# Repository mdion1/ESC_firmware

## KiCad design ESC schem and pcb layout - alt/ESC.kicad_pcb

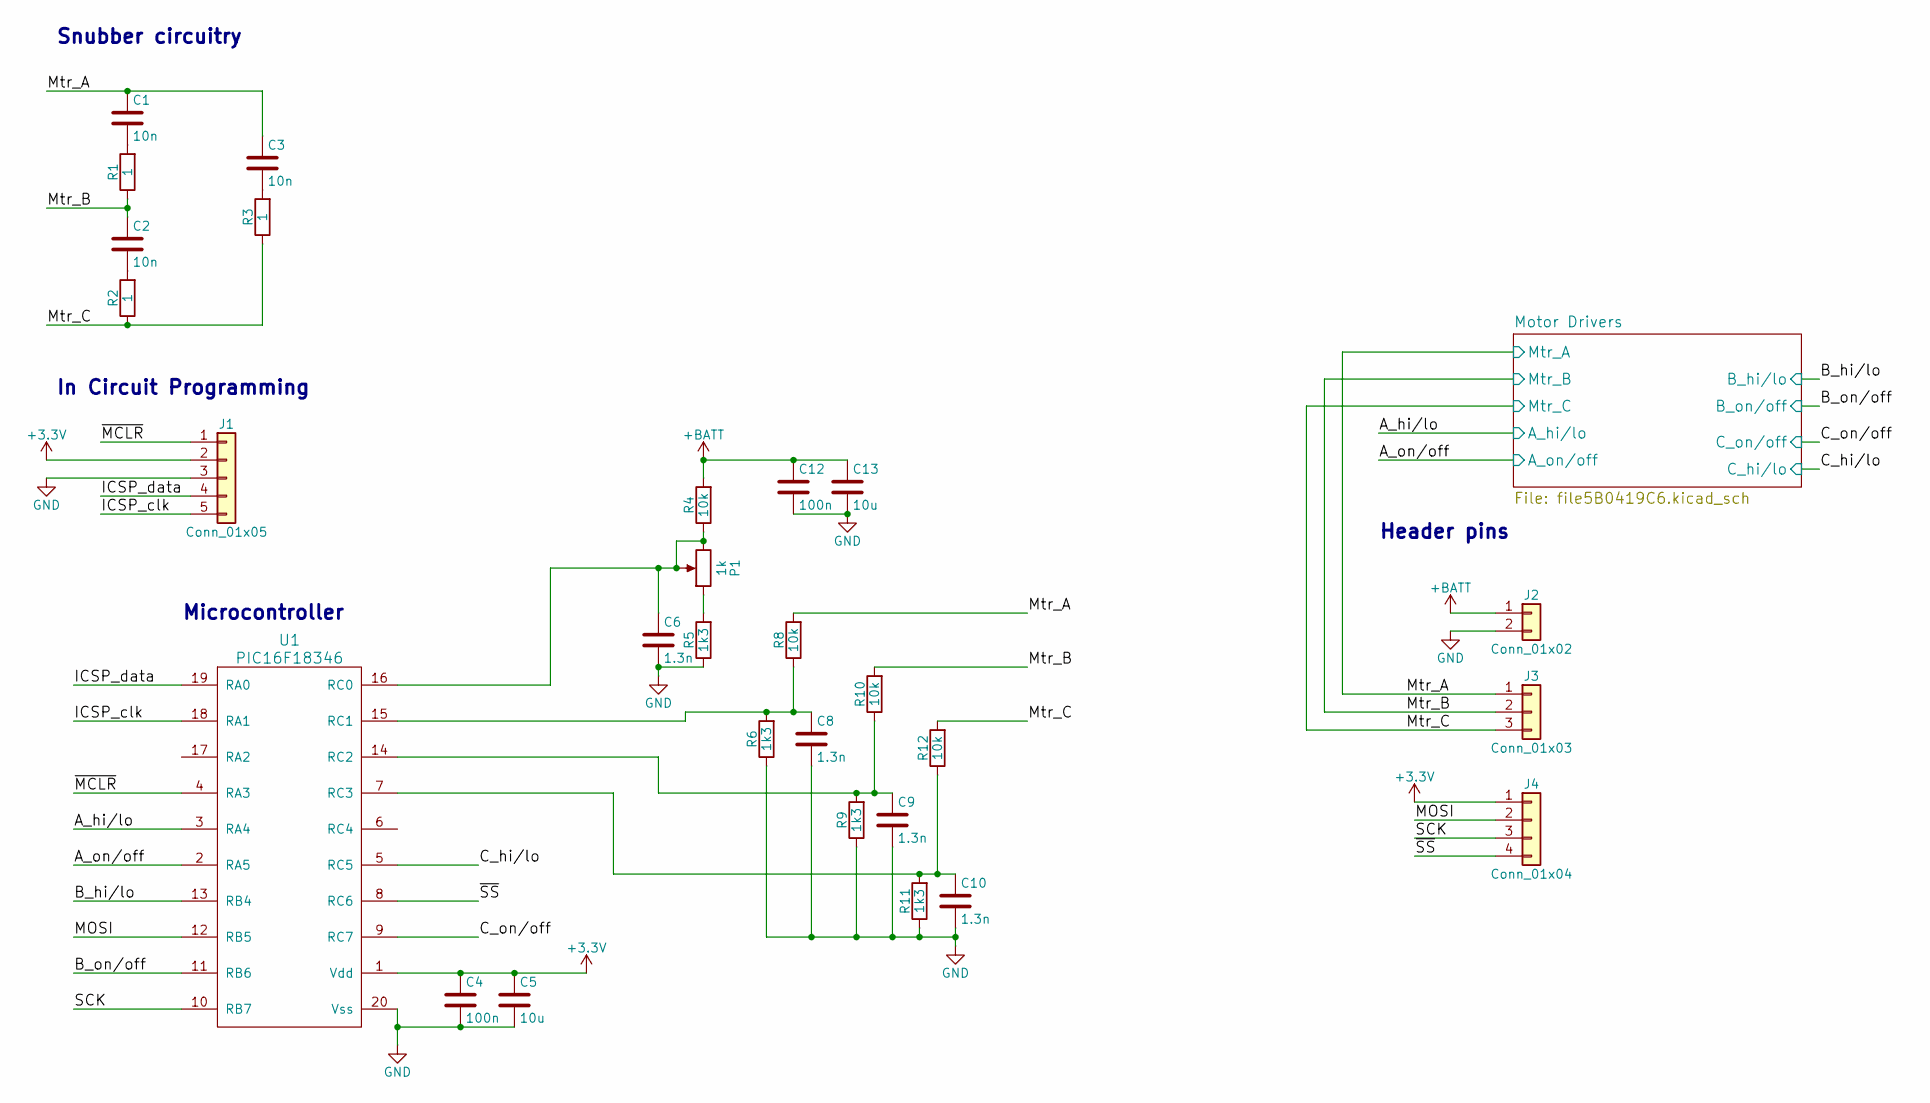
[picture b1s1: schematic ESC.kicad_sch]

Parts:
C1, C2, C3: 10n; C_0603_HandSoldering
C4, C12: 100n; C_0603_HandSoldering
C5, C13: 10u; C_0603_HandSoldering
C6, C8, C9, C10: 1.3n; C_0603_HandSoldering
J1: Conn_01x05; Male_header_pins_1x5
J2: Conn_01x02; Wire-to-board_1x2
J3: Conn_01x03; Wire-to-board_1x3
J4: Conn_01x04; Wire_to_board_cluster__4
P1: 1k; Potentiometer_Trimmer_Bourns_3223W
R1, R2, R3: 1; R_0603_HandSoldering
R4, R8, R10, R12: 10k; R_0603_HandSoldering
R5, R6, R9, R11: 1k3; R_0603_HandSoldering
U1: PIC16F18346; SOIC-20W_7.5x12.8mm_Pitch1.27mm

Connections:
+3V3: C4.1, C5.1, J1.2, J4.1, U1.1 (Vdd)
+BATT: C12.1, C13.1, J2.1, R4.2; also elsewhere on the board
/A_hi/lo: U1.3 (RA4); also elsewhere on the board
/A_on/off: U1.2 (RA5); also elsewhere on the board
/B_hi/lo: U1.13 (RB4); also elsewhere on the board
/B_on/off: U1.11 (RB6); also elsewhere on the board
/C_hi/lo: U1.5 (RC5); also elsewhere on the board
/C_on/off: U1.9 (RC7); also elsewhere on the board
/ICSP_clk: J1.5, U1.18 (RA1)
/ICSP_data: J1.4, U1.19 (RA0)
/MOSI: J4.2, U1.12 (RB5)
/Mtr_A: C1.1, C3.1, J3.1, R8.2; also elsewhere on the board
/Mtr_B: C2.1, J3.2, R1.1, R10.2; also elsewhere on the board
/Mtr_C: J3.3, R2.1, R3.1, R12.2; also elsewhere on the board
/SCK: J4.3, U1.10 (RB7)
/~MCLR: J1.1, U1.4 (RA3)
/~SS: J4.4, U1.8 (RC6)
GND: C4.2, C5.2, C6.2, C8.2, C9.2, C10.2, C12.2, C13.2, J1.3, J2.2, R5.1, R6.1, R9.1, R11.1, U1.20 (Vss); also elsewhere on the board
unnamed: C1.2, R1.2
unnamed: C2.2, R2.2
unnamed: C3.2, R3.2
unnamed: C6.1, P1.2, P1.3, R4.1, U1.16 (RC0)
unnamed: C8.1, R6.2, R8.1, U1.15 (RC1)
unnamed: C9.1, R9.2, R10.1, U1.14 (RC2)
unnamed: C10.1, R11.2, R12.1, U1.7 (RC3)
unnamed: P1.1, R5.2

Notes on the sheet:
In Circuit Programming
Header pins
Microcontroller
Snubber circuitry

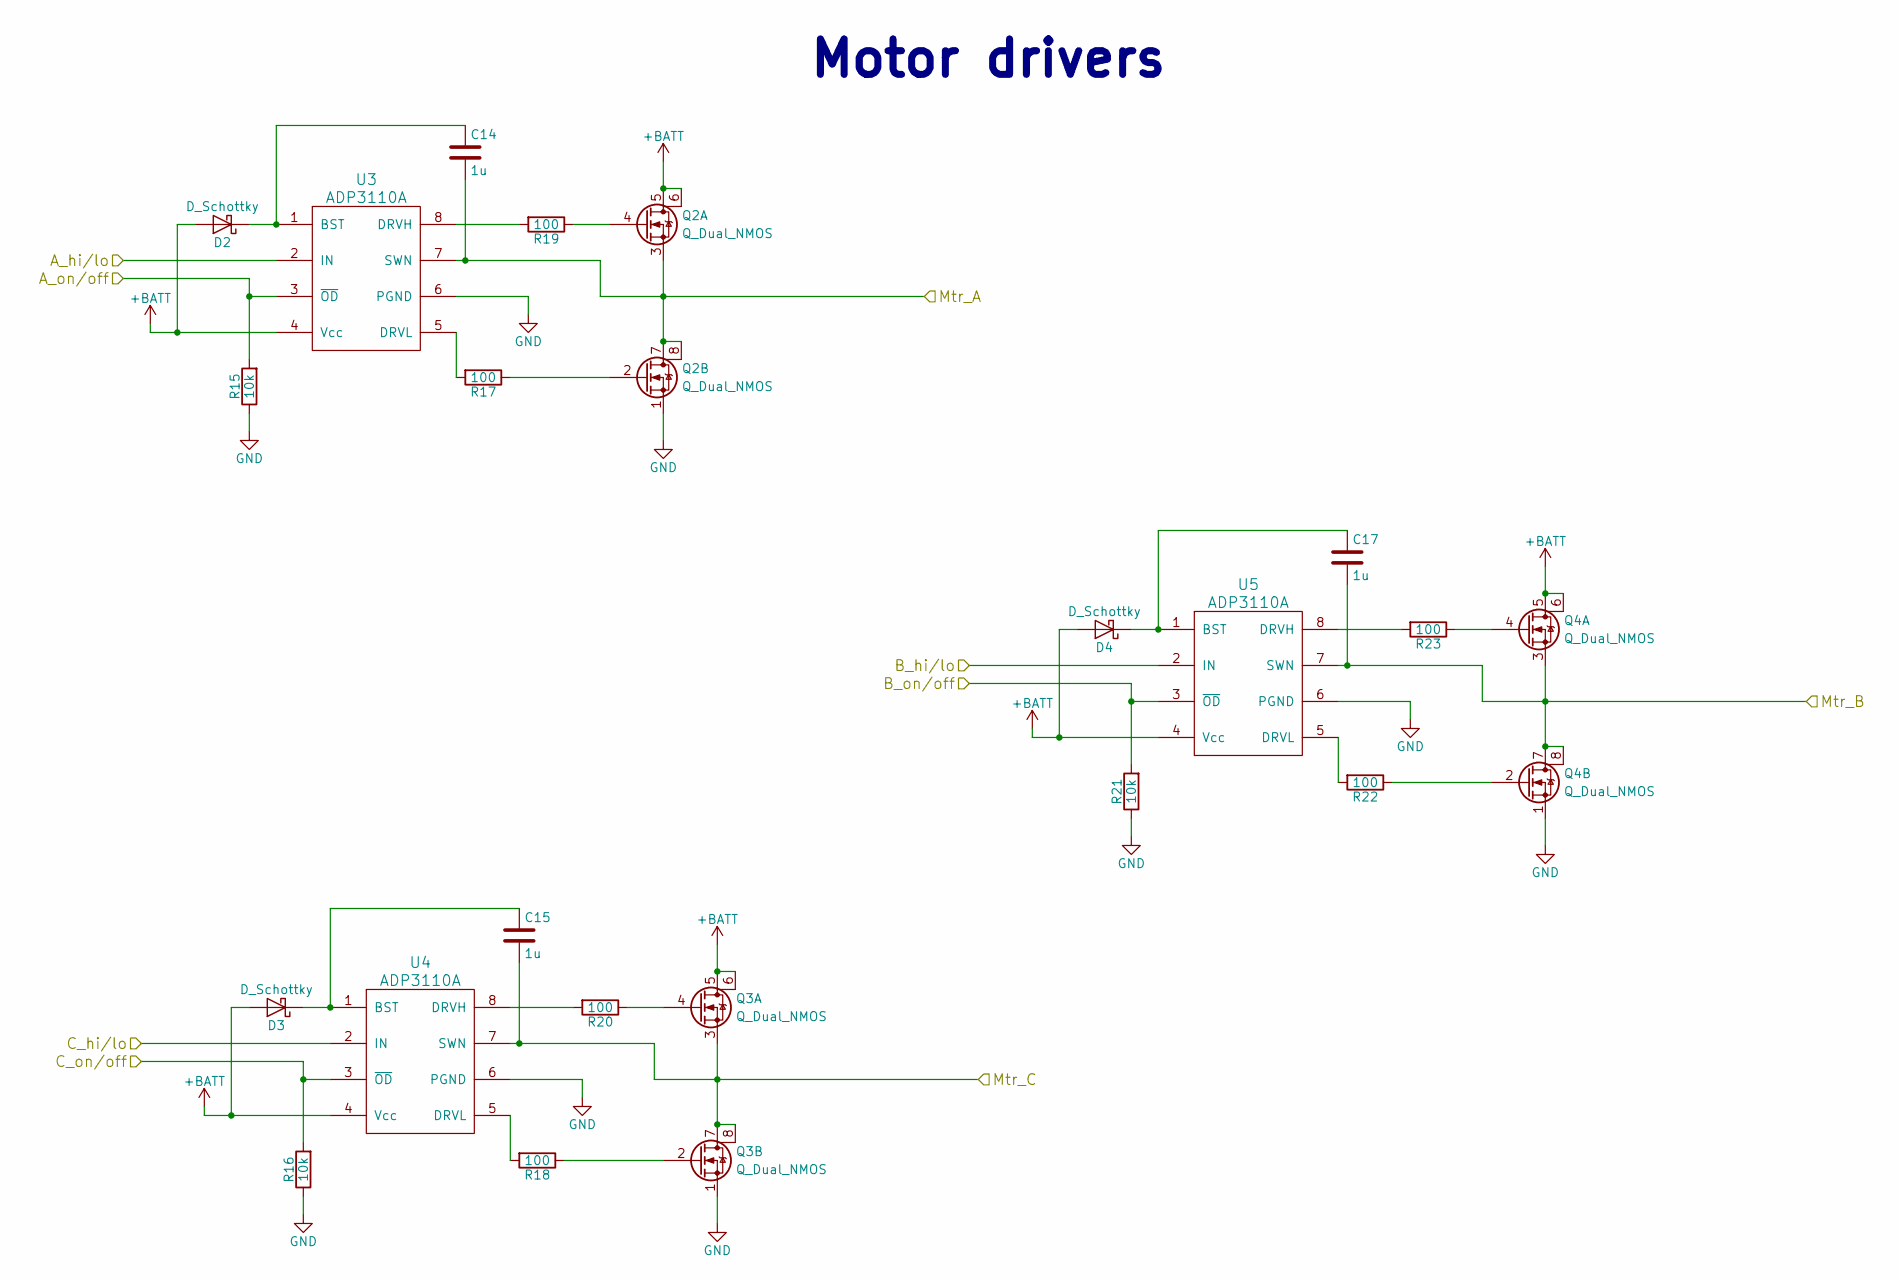
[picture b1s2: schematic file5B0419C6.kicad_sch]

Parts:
C14, C15, C17: 1u; C_0603_HandSoldering
D2, D3, D4: D_Schottky; D_0603
Q2, Q3, Q4: Q_Dual_NMOS; SOIC-8_3.9x4.9mm_Pitch1.27mm
R15, R16, R21: 10k; R_0603_HandSoldering
R17, R18, R19, R20, R22, R23: 100; R_0603_HandSoldering
U3, U4, U5: ADP3110A; SOIC-8_3.9x4.9mm_Pitch1.27mm

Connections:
+BATT: D2.2 (A), D3.2 (A), D4.2 (A), Q2.5 (D1), Q2.6 (D2), Q3.5 (D1), Q3.6 (D2), Q4.5 (D1), Q4.6 (D2), U3.4 (Vcc), U4.4 (Vcc), U5.4 (Vcc); also elsewhere on the board
/A_hi/lo: U3.2 (IN); also elsewhere on the board
/A_on/off: R15.2, U3.3 (~OD); also elsewhere on the board
/B_hi/lo: U5.2 (IN); also elsewhere on the board
/B_on/off: R21.2, U5.3 (~OD); also elsewhere on the board
/C_hi/lo: U4.2 (IN); also elsewhere on the board
/C_on/off: R16.2, U4.3 (~OD); also elsewhere on the board
/Mtr_A: C14.2, Q2.3 (S), Q2.7 (D1), Q2.8 (D2), U3.7 (SWN); also elsewhere on the board
/Mtr_B: C17.2, Q4.3 (S), Q4.7 (D1), Q4.8 (D2), U5.7 (SWN); also elsewhere on the board
/Mtr_C: C15.2, Q3.3 (S), Q3.7 (D1), Q3.8 (D2), U4.7 (SWN); also elsewhere on the board
GND: Q2.1 (S), Q3.1 (S), Q4.1 (S), R15.1, R16.1, R21.1, U3.6 (PGND), U4.6 (PGND), U5.6 (PGND); also elsewhere on the board
unnamed: C14.1, D2.1 (K), U3.1 (BST)
unnamed: C15.1, D3.1 (K), U4.1 (BST)
unnamed: C17.1, D4.1 (K), U5.1 (BST)
unnamed: Q2.2 (G2), R17.1
unnamed: Q2.4 (G2), R19.1
unnamed: Q3.2 (G2), R18.1
unnamed: Q3.4 (G2), R20.1
unnamed: Q4.2 (G2), R22.1
unnamed: Q4.4 (G2), R23.1
unnamed: R17.2, U3.5 (DRVL)
unnamed: R18.2, U4.5 (DRVL)
unnamed: R19.2, U3.8 (DRVH)
unnamed: R20.2, U4.8 (DRVH)
unnamed: R22.2, U5.5 (DRVL)
unnamed: R23.2, U5.8 (DRVH)

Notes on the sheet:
Motor drivers

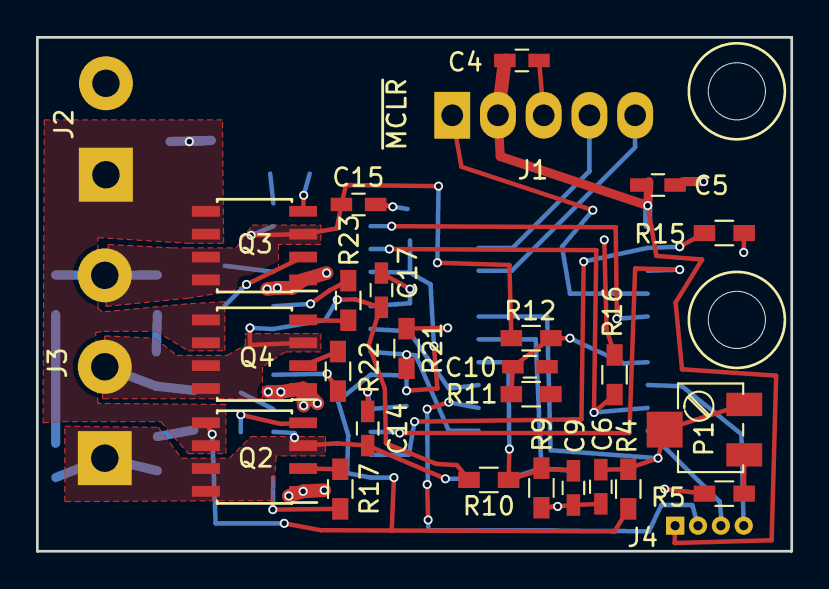
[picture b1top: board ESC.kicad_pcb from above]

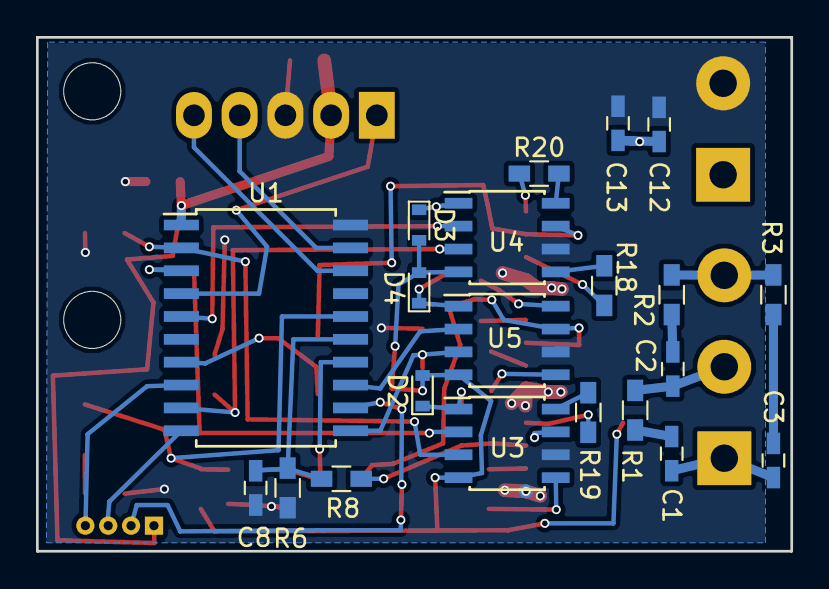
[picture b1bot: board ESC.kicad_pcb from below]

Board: 2 copper layers, 41.9 x 28.5 mm, 49 parts (21 on the bottom side), 41 nets.

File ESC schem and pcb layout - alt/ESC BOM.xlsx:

Collated Components:
Item | Qty | Reference(s) | Value | LibPart | Footprint | Datasheet | Mfr PN | Vendor | VPN
1 | 3 | C1, C2, C3 | 10n | device:C | Capacitors_SMD:C_0603_HandSoldering |  | C1608X8R1H103K080AE | Mouser | 810-C1608X8R1H103KAE
2 | 2 | C4, C12 | 100n | device:C | Capacitors_SMD:C_0603_HandSoldering |  | C1608X5R1H104K080AA | Mouser | 810-C1608X5R1H104K
3 | 2 | C5, C13 | 10u | device:C | Capacitors_SMD:C_0603_HandSoldering |  | C1608JB1E106M080AC | Mouser | 810-C1608JB1E106M08C
4 | 4 | C6, C8, C9, C10 | 1.3n | device:C | Capacitors_SMD:C_0603_HandSoldering |  | C0603C132J5GACTU | Mouser | 80-C0603C132J5GACTU
5 | 3 | C14, C15, C17 | 1u | device:C | Capacitors_SMD:C_0603_HandSoldering |  | TMK107BJ105MA-T | Mouser | 963-TMK107BJ105MA-T | Alt: share 100nF part
6 | 3 | D2, D3, D4 | D_Schottky | device:D_Schottky | Diodes_SMD:D_0603 |  | CDBU00340 | Mouser | 750-CDBU00340
7 | 1 | J1 | Conn_01x05 | conn:Conn_01x05 | ESC_footprints:Male_header_pins_1x5 |  | 42375-1247 | Mouser | 538-42375-1247
8 | 1 | J2 | Conn_01x02 | conn:Conn_01x02 | ESC_footprints:Wire-to-board_1x2 |  | n/a
9 | 1 | J3 | Conn_01x03 | conn:Conn_01x03 | ESC_footprints:Wire-to-board_1x3 |  | n/a
10 | 1 | J4 | Conn_01x04 | conn:Conn_01x04 | ESC_footprints:Wire_to_board_cluster__4 |  | n/a
11 | 1 | P1 | 1k | device:POT | ESC_footprints:Potentiometer_Trimmer_Bourns_3223W |  | 3223W-1-102 | Mouser | 652-3223W-1-102
12 | 3 | Q2, Q3, Q4 | Q_Dual_NMOS | ESC:Q_Dual_NMOS | Housings_SOIC:SOIC-8_3.9x4.9mm_Pitch1.27mm |  | AO4838 | Digikey | 785-1688-1-ND
13 | 3 | R1, R2, R3 | 1 | device:R | Resistors_SMD:R_0603_HandSoldering |  | ESR03EZPJ1R0 | Mouser | 755-ESR03EZPJ1R0
14 | 7 | R4, R8, R10, R12, R15, R16, R21 | 10k, 0.1% | device:R | Resistors_SMD:R_0603_HandSoldering |  | APC0603B10K0N | Mouser | 284-APC0603B10K0N
15 | 4 | R5, R6, R9, R11 | 1k3, 0.1% | device:R | Resistors_SMD:R_0603_HandSoldering |  | ERJ-PB6B1301V | Mouser | 667-ERJ-PB6B1301V
16 | 6 | R17, R18, R19, R20, R22, R23 | 100 | device:R | Resistors_SMD:R_0603_HandSoldering |  | CRCW0603100RFKEAC | Mouser | 71-CRCW0603100RFKEAC
17 | 1 | U1 | PIC16F18346 | ESC:PIC16F18346 | Housings_SOIC:SOIC-20W_7.5x12.8mm_Pitch1.27mm |  | PIC16F18346-I/SO | Mouser | 579-PIC16F18346-I/SO
18 | 3 | U3, U4, U5 | ADP3110A | ESC:ADP3110A | Housings_SOIC:SOIC-8_3.9x4.9mm_Pitch1.27mm |  | ADP3110A | Mouser | 863-ADP3110AKRZ-RL

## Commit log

2018-06-14 Simple open-loop control, fixed PWM, directly-controlled commutation period
2018-07-04 Basic functionality confirmed, moving on to automatic open- and closed-loop control
2018-07-10 Fixed some bugs, but comparator still triggers early
2018-07-10 Added comparator output pin for easier debugging of comparator triggering
2019-06-27 include project files
2019-09-04 Initial commit, added Arduino project to run motor using Teensy 3.2
2019-09-05 comparator and PWM power up and work
2019-09-06 Untested code, links CMP rising edge to timer input capture; adds interrupts for commutation timer and comparator
2019-09-08 Syntax errors, minor changes before testing: DMA only initialized with USE_DMA_CHANNEL define; DMAMUX trigger source was incorrect; set up test for commutation timer overflow
2019-09-09 forgot NVIC_ENABLE_IRQ() macro (where is this defined?); FTM1_C0SC had bits set by default that need to be cleared
2019-09-11 Open loop mode works; bug--commutation timer prescaler is off by factor of 2
2019-09-22 Bug: motor commutation order was wrong, cmp phase was out of order (it's only fixed for CCW mode); control loop works up to ~2500rpm
2019-09-22 Added in a filtered derivative tracker to help damped oscillation
2019-09-29 Caught a couple bugs, one in recalculate_commutation_time() and one in the timer interrupt; added debugging_buf class
2019-09-29 Tweaked deriv filter size and limits, implemented negative deriv control
2023-04-29 Added old revisions + rev2 (WIP)
